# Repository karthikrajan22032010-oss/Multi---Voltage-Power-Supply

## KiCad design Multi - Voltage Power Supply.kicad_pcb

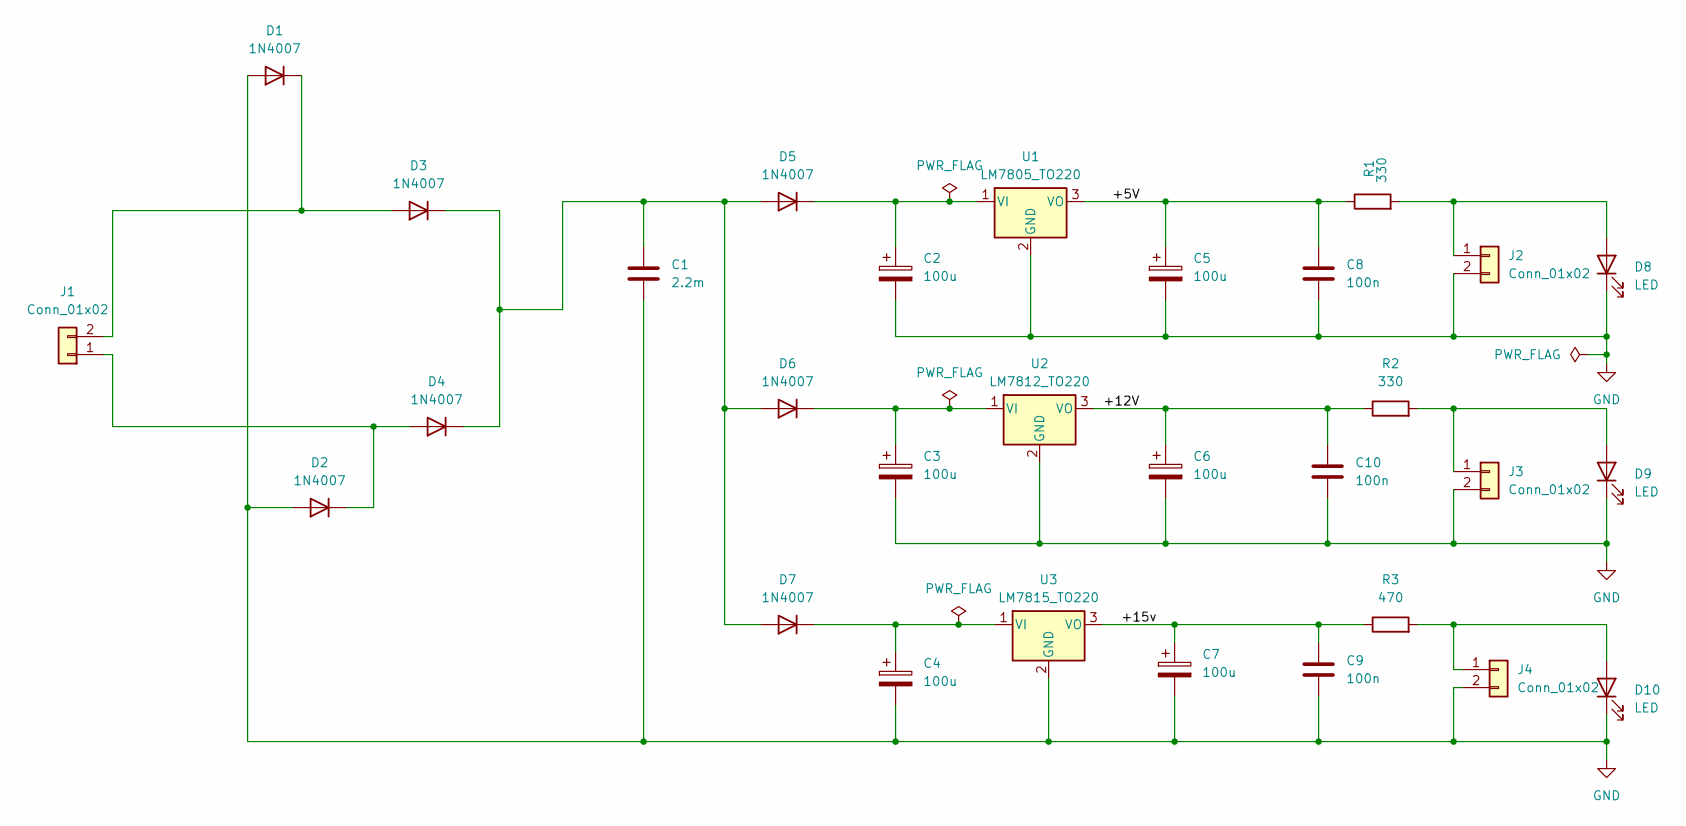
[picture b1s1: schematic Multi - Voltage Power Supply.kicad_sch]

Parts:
C1: 2.2m; CP_Elec_4x3
C2, C3, C4, C5, C6, C7: 100u; CP_Elec_4x5.8
C8, C9, C10: 100n; C_1812_4532Metric_Pad1.57x3.40mm_HandSolder
D1, D2, D3, D4: 1N4007; D_0201_0603Metric
D5, D6, D7: 1N4007; D_0402_1005Metric
D8, D9, D10: LED; LED_D3.0mm
J1, J2, J3, J4: Conn_01x02; PinHeader_1x02_P2.54mm_Vertical
R1, R2: 330; R_0603_1608Metric
R3: 470; R_0603_1608Metric
U1: LM7805_TO220; Analog_KS-4
U2: LM7812_TO220; Analog_KS-4
U3: LM7815_TO220; Analog_KS-4

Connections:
/+5V: C5.1, C8.1, R1.1, U1.3 (VO)
/+12V: C6.1, C10.1, R2.1, U2.3 (VO)
/+15v: C7.1, C9.1, R3.1, U3.3 (VO)
GND: C1.2, C2.2, C3.2, C4.2, C5.2, C6.2, C7.2, C8.2, C9.2, C10.2, D1.2 (A), D2.2 (A), D8.1 (K), D9.1 (K), D10.1 (K), J2.2, J3.2, J4.2, U1.2 (GND), U2.2 (GND), U3.2 (GND)
unnamed: D1.1 (K), D3.2 (A), J1.2
unnamed: D2.1 (K), D4.2 (A), J1.1
unnamed: C1.1, D3.1 (K), D4.1 (K), D5.2 (A), D6.2 (A), D7.2 (A)
unnamed: C2.1, D5.1 (K), U1.1 (VI)
unnamed: C3.1, D6.1 (K), U2.1 (VI)
unnamed: C4.1, D7.1 (K), U3.1 (VI)
unnamed: D8.2 (A), J2.1, R1.2
unnamed: D9.2 (A), J3.1, R2.2
unnamed: D10.2 (A), J4.1, R3.2

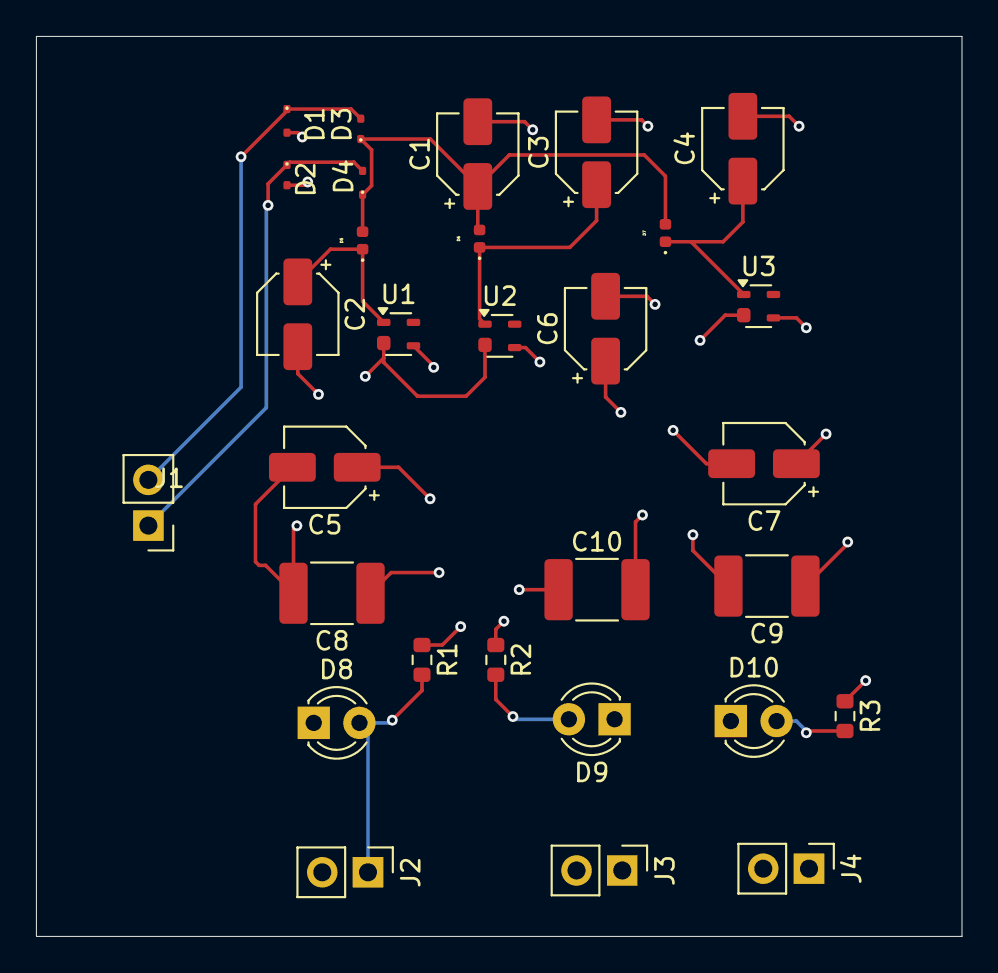
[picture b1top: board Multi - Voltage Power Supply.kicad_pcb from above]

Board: 4 copper layers, 51.4 x 50.0 mm, 30 parts (0 on the bottom side), 13 nets.
